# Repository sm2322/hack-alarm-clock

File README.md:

# My Alarm Clock!
- Single board PCB
- Connect screen horizontally to pcb
- It has three buttons!
 	- Up, Down, Confirm
- Custom designed case that is 3d printed in three parts
- Easy assembly with secure wiring
- It has custom made firmware that let's you set an alarm and set the current time

## Journal
### Day 1
  - Started the project! Wrote out a plan in Obsidian and downlaoded the footprints off github.
  - Imported the footprints into kicad
- Just finished my first version of pcb! Looks good. and getting this far took about an hour 26 mins. It has a vertical screen and three buttons on top. Time for modelling. Pray for me
- [Lapse](https://lapse.hackclub.com/timelapse/gpTg3AW5xFuO) 1 Hour 26 Min of work

- WHOOOOO I built the entire v1 of the case design in one sitting
- It has been a very productive afternoon but we have deadlines
- Almost firmware time.
- The case is a three piece design meant to be 3d printed. I think it will work well i leanred from my mistakes and it is very chamfered and secure hopefully.
[Lapse](https://lapse.hackclub.com/timelapse/pJ3X7i8eazS0) 2 Hours of Work

### DAY 2
- I built the firmware and learned how to program in arduino
- Conencted the components and began working in the IDE as well as TinkerCad
 -  [Lapse](https://lapse.hackclub.com/timelapse/GXq9KAY2PaT6) 47 Minutes of work

- Added the ability to set the time on the clock
- Added the ability to set the alarm time too!
-  [Lapse](https://lapse.hackclub.com/timelapse/48aM7OdNLg47 1 Hour of work

Full Hackatime Project
[Hackatime - Track your coding time](https://hackatime.hackclub.com/my/projects/BLARE%20alarm%20clock) 5 Hours 21 Mins of work total :)

# Roadmap
- Add support for the buzzer to properly go off
- Add support for the display correctly once I get it for easier debug
- Add AM/PM support
- Make it look more pretty :)
# BOM
- 1x Lolin C3 Mini ESP 32 Devboard
- 3x Keyboard Switches
- 3x Keycap
- 1x 2.25in TFT Screen
- 1x 3.3V Piezo Buzzer
- 1x Custom PCB
- 1x 3d Printed Casing

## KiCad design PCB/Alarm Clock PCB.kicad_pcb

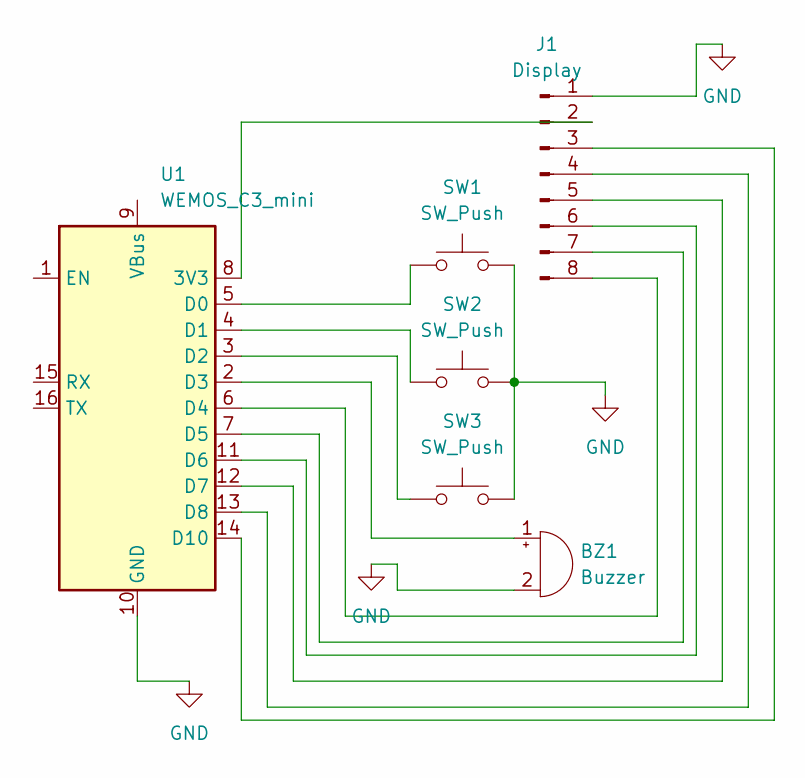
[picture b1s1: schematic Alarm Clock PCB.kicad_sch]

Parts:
BZ1: Buzzer; Buzzer_12x9.5RM7.6
J1: Display; PinHeader_1x08_P2.54mm_Horizontal
SW1, SW2, SW3: SW_Push; SW_Cherry_MX_1.00u_PCB
U1: WEMOS_C3_mini

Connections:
GND: BZ1.2 (-), J1.1, SW1.2, SW2.2, SW3.2, U1.10 (GND)
unnamed: BZ1.1 (+), U1.2 (D3)
unnamed: J1.2, U1.8 (3V3)
unnamed: J1.3, U1.14 (D10)
unnamed: J1.4, U1.13 (D8)
unnamed: J1.5, U1.12 (D7)
unnamed: J1.6, U1.11 (D6)
unnamed: J1.7, U1.7 (D5)
unnamed: J1.8, U1.6 (D4)
unnamed: SW1.1, U1.5 (D0)
unnamed: SW2.1, U1.4 (D1)
unnamed: SW3.1, U1.3 (D2)

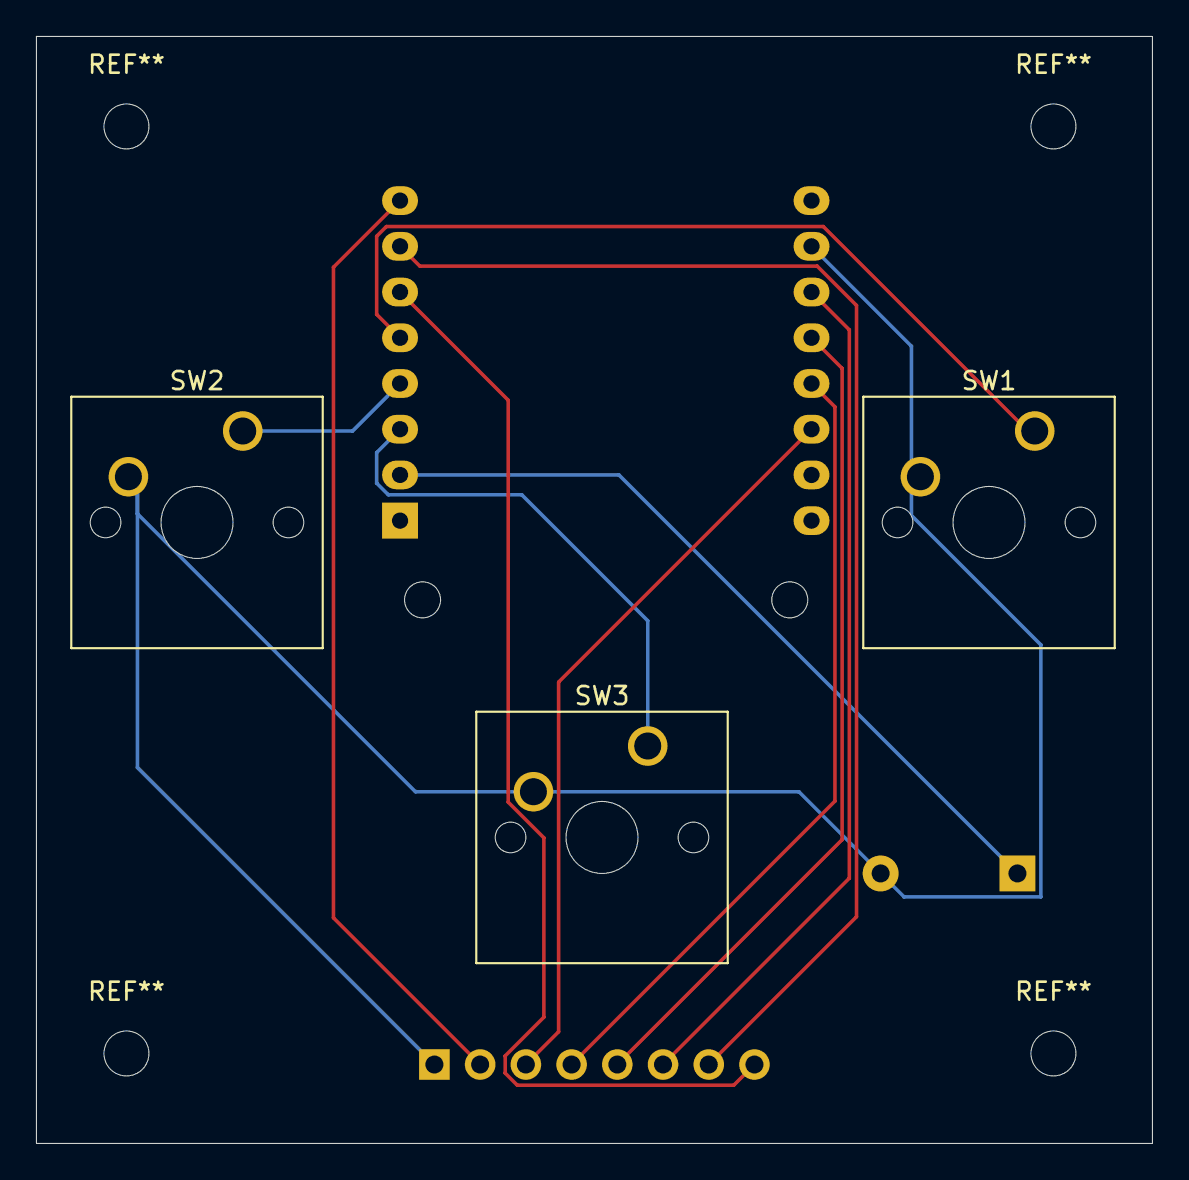
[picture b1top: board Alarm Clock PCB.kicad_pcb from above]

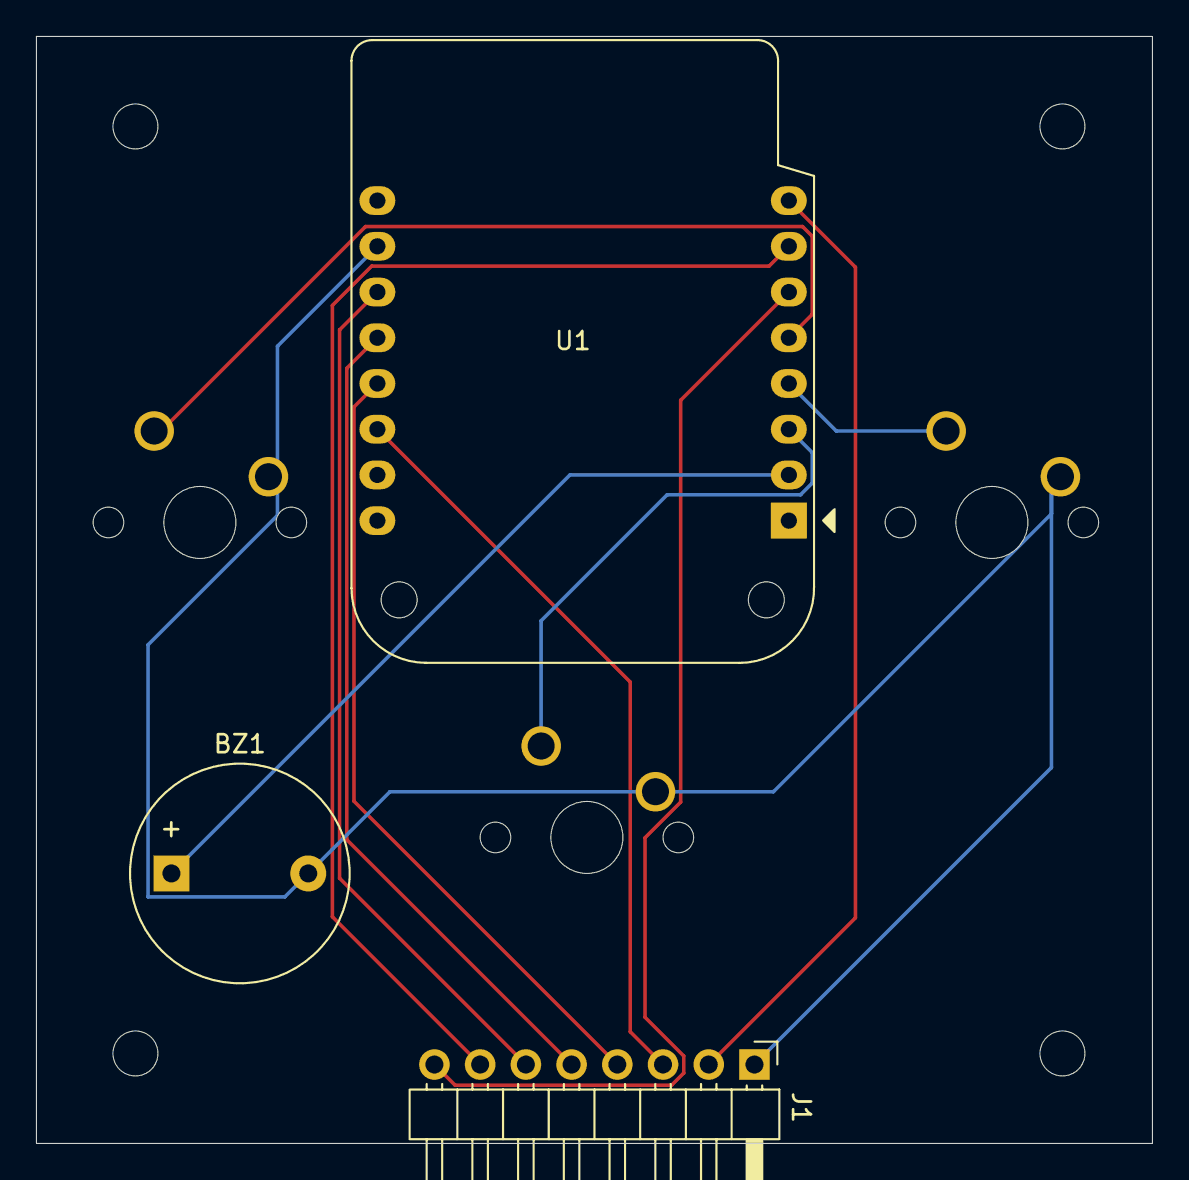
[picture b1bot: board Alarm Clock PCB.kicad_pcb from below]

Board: 2 copper layers, 62.0 x 61.5 mm, 6 parts (3 on the bottom side), 12 nets.
